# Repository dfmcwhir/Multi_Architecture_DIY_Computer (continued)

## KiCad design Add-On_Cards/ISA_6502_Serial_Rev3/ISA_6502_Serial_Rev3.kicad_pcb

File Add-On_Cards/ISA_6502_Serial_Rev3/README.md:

#<h2> ISA_6502_Serial_Rev3 </h2>
<p>This is a new card that is in the process of being tested with the ISA_6502_CPU Rev2 card. It hasn't been tested at all with the ISA_6502_CPU rev1 or other CPU cards yet. It has the same 6551 ACIA chip and MAX232 serial interface, but now a PS2 keyboard and mouse interface has been moved to this board. The keyboard and mouse interfaces to the bus using an ATMEGA328 microcontroller. The code for the ATMEGA238 is based on Grant Searle code here: http://searle.x10host.com/MonitorKeyboard/index.html. The ATMEGA also provides a TTL serial console interface that can be read from and written to. This is for providing a UI when you don't have a keyboard and display hooked up to the computer without having to dedicate the card's main serial interface to that.</p>

<h2>Resources</h2>
<table><thead><tr><th>Address</th><th>Function</th></tr></thead>
<tr><td>7F14</td><td>Serial Data Register</td></tr>
<tr><td>7F15</td><td>Serial Status Register</td></tr>
<tr><td>7F16</td><td>Serial Command Register</td></tr>
<tr><td>7F17</td><td>Serial Control Register</td></tr>
<tr><td>7F1E</td><td>Read=KB/mouse data, Write=serial console out/td></tr>
<tr><td>7F1F</td><td>Read=KB status, D7=KBavail,D6=DBusy</td></tr>
</table>

<p>The 6551 uses IRQ3. The keyboard/mouse uses IRQ5 or 6 (selectable by a jumper). Previously, when the kb and the display were on one card it used IRQ5, but jumper allows for more flexibility.</p>

<h2>Testing Status:</h2>
<p>The KB and mouse interface has been tested and seems to work with the FW uploaded. The ACIA Serial and console serial hasn't been tested yet. It hasn't been tested with any CPU cards other than the 6502_CPU Rev2 card. </p>

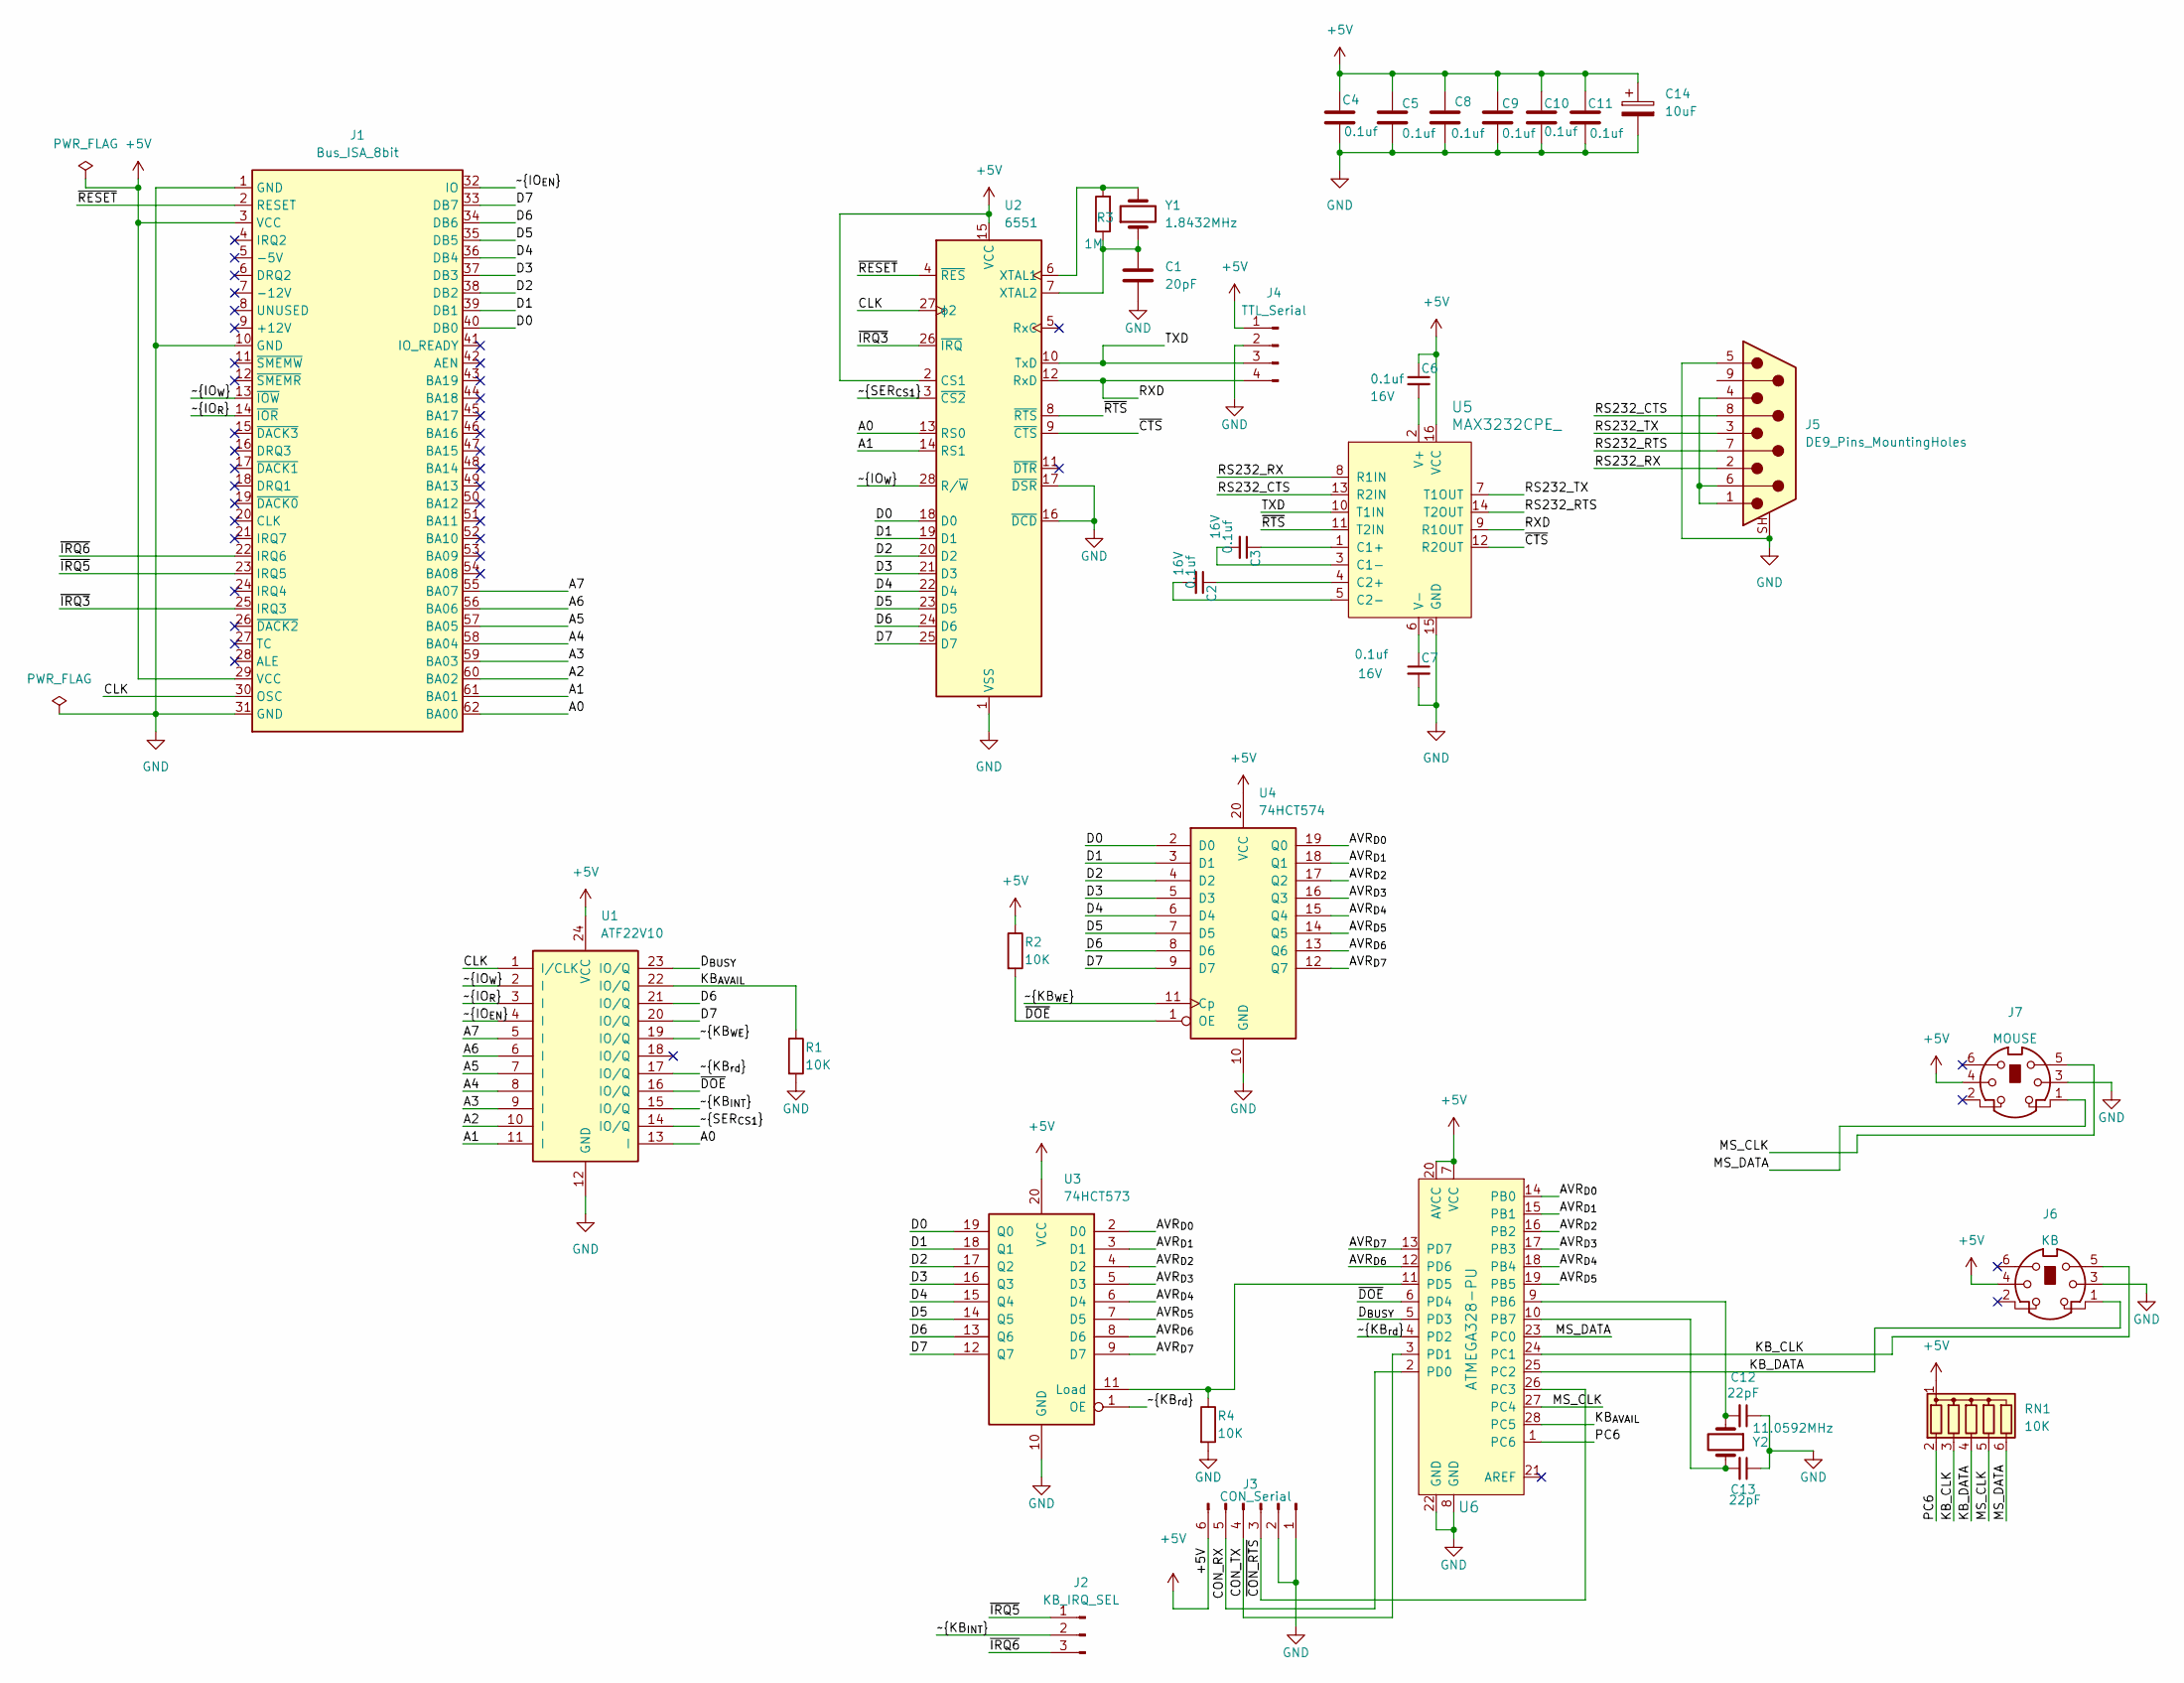
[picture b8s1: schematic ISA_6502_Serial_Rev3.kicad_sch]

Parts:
C1: 20pF; C_Disc_D4.7mm_W2.5mm_P5.00mm
C2, C3, C6, C7: 0.1uf; C_Disc_D4.7mm_W2.5mm_P5.00mm; Voltage 16V; Tolerance 100%
C4, C5, C8, C9, C10, C11: 0.1uf; C_Disc_D4.7mm_W2.5mm_P5.00mm
C12, C13: 22pF; C_Disc_D4.7mm_W2.5mm_P5.00mm; Voltage 50V; Tolerance 5%
C14: 10uF; CP_Radial_D5.0mm_P2.00mm
J1: Bus_ISA_8bit; BUS_8-bit_ISA_CARD
J2: KB_IRQ_SEL; PinHeader_1x03_P2.54mm_Vertical
J3: CON_Serial; PinHeader_1x06_P2.54mm_Vertical
J4: TTL_Serial; PinHeader_1x04_P2.54mm_Vertical
J5: DE9_Pins_MountingHoles; DSUB-9_Pins_Horizontal_P2.77x2.84mm_EdgePinOffset7.70mm_Hou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
J6: KB; Connector_Mini-DIN_Female_6Pin_2rows
J7: MOUSE; Connector_Mini-DIN_Female_6Pin_2rows
R1, R2, R4: 10K; R_Axial_DIN0207_L6.3mm_D2.5mm_P10.16mm_Horizontal
R3: 1M; R_Axial_DIN0207_L6.3mm_D2.5mm_P10.16mm_Horizontal
RN1: 10K; R_Array_SIP6
U1: ATF22V10; DIP-24_W7.62mm
U2: 6551; DIP-28_W15.24mm
U3: 74HCT573; DIP-20_W7.62mm
U4: 74HCT574; DIP-20_W7.62mm
U5: MAX3232CPE_; DIP-16_W7.62mm; MPN MAX3232CPE+; Digi-Key_PN MAX3232CPE+-ND
U6: ATMEGA328-PU; DIP-28_W7.62mm_Socket; MPN ATMEGA328-PU; Digi-Key_PN ATMEGA328-PU-ND
Y1: 1.8432MHz; Crystal_HC18-U_Vertical
Y2: 11.0592MHz; Crystal_HC18-U_Vertical

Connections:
+5V: C4.1, C5.1, C6.1, C8.1, C9.1, C10.1, C11.1, C14.1, J1.3 (VCC), J1.29 (VCC), J3.6, J4.1, J6.4, J7.4, R2.1, RN1.1 (common), U1.24 (VCC), U2.2 (CS1), U2.15 (VCC), U3.20 (VCC), U4.20 (VCC), U5.16 (VCC), U6.7 (VCC), U6.20 (AVCC)
/A0: J1.62 (BA00), U1.13 (I), U2.13 (RS0)
/A1: J1.61 (BA01), U1.11 (I), U2.14 (RS1)
/A2: J1.60 (BA02), U1.10 (I)
/A3: J1.59 (BA03), U1.9 (I)
/A4: J1.58 (BA04), U1.8 (I)
/A5: J1.57 (BA05), U1.7 (I)
/A6: J1.56 (BA06), U1.6 (I)
/A7: J1.55 (BA07), U1.5 (I)
/AVR_{D0}: U3.2 (D0), U4.19 (Q0), U6.14 (PB0)
/AVR_{D1}: U3.3 (D1), U4.18 (Q1), U6.15 (PB1)
/AVR_{D2}: U3.4 (D2), U4.17 (Q2), U6.16 (PB2)
/AVR_{D3}: U3.5 (D3), U4.16 (Q3), U6.17 (PB3)
/AVR_{D4}: U3.6 (D4), U4.15 (Q4), U6.18 (PB4)
/AVR_{D5}: U3.7 (D5), U4.14 (Q5), U6.19 (PB5)
/AVR_{D6}: U3.8 (D6), U4.13 (Q6), U6.12 (PD6)
/AVR_{D7}: U3.9 (D7), U4.12 (Q7), U6.13 (PD7)
/CLK: J1.30 (OSC), U1.1 (I/CLK), U2.27 (ϕ2)
/CON_RX: J3.5, U6.2 (PD0)
/CON_TX: J3.4, U6.3 (PD1)
/D0: J1.40 (DB0), U2.18 (D0), U3.19 (Q0), U4.2 (D0)
/D1: J1.39 (DB1), U2.19 (D1), U3.18 (Q1), U4.3 (D1)
/D2: J1.38 (DB2), U2.20 (D2), U3.17 (Q2), U4.4 (D2)
/D3: J1.37 (DB3), U2.21 (D3), U3.16 (Q3), U4.5 (D3)
/D4: J1.36 (DB4), U2.22 (D4), U3.15 (Q4), U4.6 (D4)
/D5: J1.35 (DB5), U2.23 (D5), U3.14 (Q5), U4.7 (D5)
/D6: J1.34 (DB6), U1.21 (IO/Q), U2.24 (D6), U3.13 (Q6), U4.8 (D6)
/D7: J1.33 (DB7), U1.20 (IO/Q), U2.25 (D7), U3.12 (Q7), U4.9 (D7)
/D_{BUSY}: U1.23 (IO/Q), U6.5 (PD3)
/KB_CLK: J6.5, RN1.3 (R2), U6.24 (PC1)
/KB_DATA: J6.1, RN1.4 (R3), U6.25 (PC2)
/KB_{AVAIL}: R1.1, U1.22 (IO/Q), U6.28 (PC5)
/MS_CLK: J7.5, RN1.5 (R4), U6.27 (PC4)
/MS_DATA: J7.1, RN1.6 (R5), U6.23 (PC0)
/PC6: RN1.2 (R1), U6.1 (PC6)
/RS232_CTS: J5.8, U5.13 (R2IN)
/RS232_RTS: J5.7, U5.14 (T2OUT)
/RS232_RX: J5.2, U5.8 (R1IN)
/RS232_TX: J5.3, U5.7 (T1OUT)
/RXD: J4.4, U2.12 (RxD), U5.9 (R1OUT)
/TXD: J4.3, U2.10 (TxD), U5.10 (T1IN)
/~CON_RTS: J3.3, U6.26 (PC3)
/~CTS: U2.9 (~CTS), U5.12 (R2OUT)
/~DOE: R2.2, U1.16 (IO/Q), U4.1 (OE), U6.6 (PD4)
/~IO_{EN}: J1.32 (IO), U1.4 (I)
/~IO_{R}: J1.14 (~IOR), U1.3 (I)
/~IO_{W}: J1.13 (~IOW), U1.2 (I), U2.28 (R/~W)
/~IRQ3: J1.25 (IRQ3), U2.26 (~IRQ)
/~IRQ5: J1.23 (IRQ5), J2.1
/~IRQ6: J1.22 (IRQ6), J2.3
/~KB_{INT}: J2.2, U1.15 (IO/Q)
/~KB_{WE}: U1.19 (IO/Q), U4.11 (Cp)
/~KB_{rd}: U1.17 (IO/Q), U3.1 (OE), U6.4 (PD2)
/~RESET: J1.2 (RESET), U2.4 (~RES)
/~RTS: U2.8 (~RTS), U5.11 (T2IN)
/~SER_{CS1}: U1.14 (IO/Q), U2.3 (~CS2)
GND: C1.2, C4.2, C5.2, C7.2, C8.2, C9.2, C10.2, C11.2, C12.1, C13.1, C14.2, J1.1 (GND), J1.10 (GND), J1.31 (GND), J3.1, J3.2, J4.2, J5.5, J5.SH (PAD), J6.3, J7.3, R1.2, R4.2, U1.12 (GND), U2.1 (VSS), U2.16 (~DCD), U2.17 (~DSR), U3.10 (GND), U4.10 (GND), U5.15 (GND), U6.8 (GND), U6.22 (GND)
unnamed: J5.1, J5.4, J5.6
unnamed: R3.2, U2.6 (XTAL1), Y1.2
unnamed: C1.1, R3.1, U2.7 (XTAL2), Y1.1
unnamed: R4.1, U3.11 (Load), U6.11 (PD5)
unnamed: C3.1, U5.1 (C1+)
unnamed: C3.2, U5.3 (C1-)
unnamed: C2.1, U5.4 (C2+)
unnamed: C2.2, U5.5 (C2-)
unnamed: C6.2, U5.2 (V+)
unnamed: C7.1, U5.6 (V-)
unnamed: C12.2, U6.9 (PB6), Y2.1
unnamed: C13.2, U6.10 (PB7), Y2.2

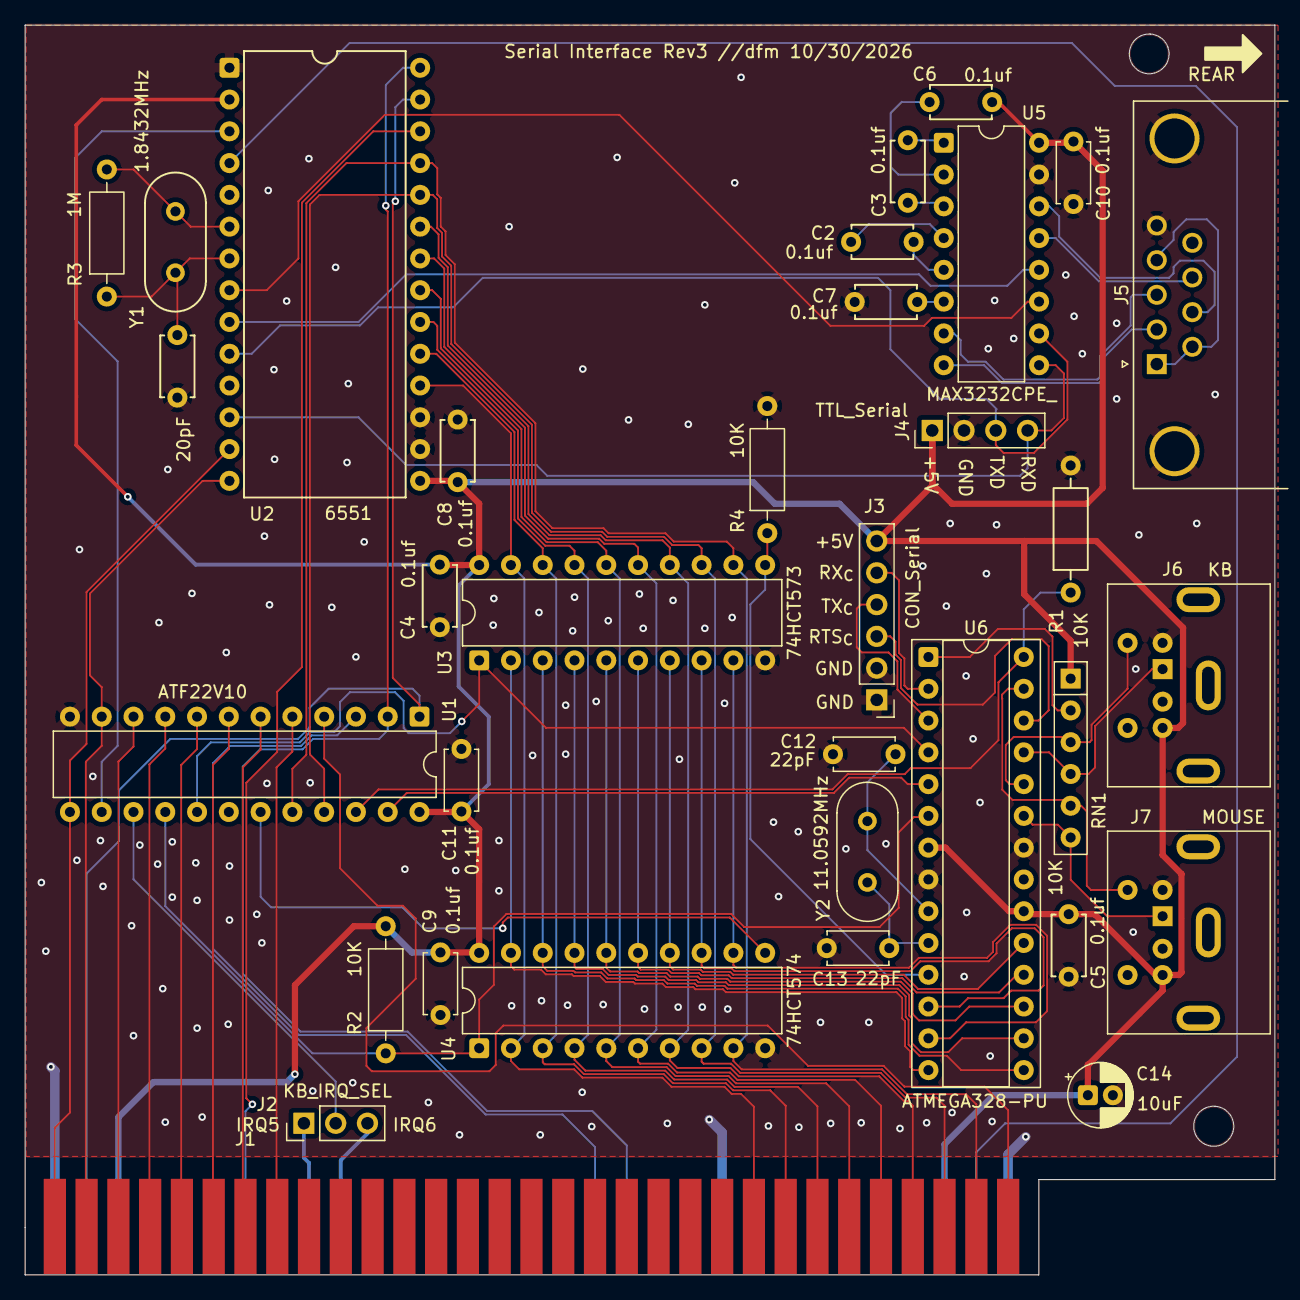
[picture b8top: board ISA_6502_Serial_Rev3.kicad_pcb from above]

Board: 2 copper layers, 99.9 x 99.9 mm, 34 parts (0 on the bottom side), 69 nets.

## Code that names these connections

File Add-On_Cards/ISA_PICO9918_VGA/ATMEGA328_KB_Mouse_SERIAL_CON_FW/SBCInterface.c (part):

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// The display output of the original (8-bit, 4-bit and TWI display links and
// the ANSI interpreter) has been removed - the PICO9918 is the display now.
//
// Version 2: adds a PS/2 mouse on PC4 (clock) and PC0 (data).
// Version 2.1: host -> device bytes (the mouse's reset and enable, the
//   keyboard's LED command) are clocked out on the falling edges, as the
//   PS/2 standard says; v2.0 was one clock edge off, so the mouse was never
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//
// ATmega328P pin use (DIP-28, 11.0592 MHz crystal)
// ------------------------------------------------
//   PB0-PB5  AVR bus D0-D5  (to '573 D inputs and '574 Q outputs)
//   PD6-PD7  AVR bus D6-D7
//   PB6-PB7  crystal
//   PC0      MOUSE DATA  (pull-up 4.7k-10k)   - was the optional /CTS input
//   PC1      KB clock    (pull-up)
//   PC2      KB data     (pull-up)
//   PC3      /RTS out
//   PC4      MOUSE CLOCK (pull-up 4.7k-10k)
//   PC5      KBAVAIL out -> GAL pin 14   (10k pull-down)
//   PC6      /RESET - keep it as reset (using it as I/O needs the RSTDISBL
//            fuse, which stops ISP programming)
//   PD0      RXD
//   PD1      TXD
//   PD2      INT0 <- /KBRD (GAL pin 17)  - byte acknowledge
//   PD3      <- DBUSY (GAL pin 22)       - 6502 has written a TX byte
//   PD4      /DOE  -> '574 /OE and GAL pin 23 (10k pull-up)
//   PD5      LE    -> '573 LE (10k pull-down)
//
// Handshakes
// ----------
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#include <stdint.h>

// ---------------------------------------------------------------- pins
#define KBAVAIL_BIT  PC5
#define RTS_BIT      PC3
#define KB_CLK_BIT   PC1
#define KB_DATA_BIT  PC2
#define MS_CLK_BIT   PC4
#define MS_DATA_BIT  PC0
#define DBUSY_BIT    PD3
#define DOE_BIT      PD4
#define LE_BIT       PD5

#define BUS_B_MASK   0x3F   // PB0-PB5 = D0-D5
#define BUS_D_MASK   0xC0   // PD6-PD7 = D6-D7

// ---------------------------------------------------------------- PS/2 devices
typedef struct
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		}
		else
		{
			d->writeActive = 0;                 // 11: the device's ack bit
			d->bitCount = 0;                    // (its rising edge is then
			d->shift = 0;                       //  ignored by the receiver)
		}
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	}
}

// Keyboard clock (PC1) and mouse clock (PC4) both raise PCINT1
ISR(PCINT1_vect)
{
	uint8_t pinc = PINC;
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	hostIn = hostOut = 0;
	txIn = txOut = 0;

	// AVR bus: inputs, no pull-ups (PB6/PB7 are the crystal)
	DDRB = 0x00;
	PORTB = 0x00;

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
	// Port D: /DOE high (set before enabling the output), LE low,
	// pull-up on the /KBRD input
	PORTD = (1 << DOE_BIT) | (1 << PD2);
	DDRD = (1 << PD1) | (1 << DOE_BIT) | (1 << LE_BIT);

	// Clear any DBUSY left set at power-up: hold /DOE low for a few clocks
	PORTD &= ~(1 << DOE_BIT);
	_delay_us(20);
	PORTD |= (1 << DOE_BIT);

	// PS/2 clocks: PC1 (keyboard) and PC4 (mouse) pin-change interrupts
	lastPinC = PINC;
	PCICR = 1 << PCIE1;
	PCMSK1 = (1 << PCINT9) | (1 << PCINT12);

	// INT0 (PD2, /KBRD) on rising edge = end of the 6502's read
	EICRA = (1 << ISC01) | (1 << ISC00);
	EIFR = 1 << INTF0;
	EIMSK = 1 << INT0;
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
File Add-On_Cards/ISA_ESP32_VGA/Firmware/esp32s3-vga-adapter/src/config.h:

// ESP32-S3 VGA / keyboard / mouse / sound adapter for a W65C02S computer.
// Pin map and build-time configuration.
//
// Board: ESP32-S3-DevKitC-1 (WROOM-1 N16R8 or N8R2 etc.). GPIO 33-37 are left
// free because octal-PSRAM modules use them. GPIO 19/20 are the native USB
// pins (USB host for keyboard/mouse). GPIO 43/44 stay as UART0 for upload and
// debug through the board's "UART" USB port.
#pragma once
#include <stdint.h>

// ---------------------------------------------------------------- 6502 bus
// All bus pins must be < 32 so one read of GPIO_IN_REG captures everything.
// D0..D7 must be consecutive GPIOs starting at PIN_D0.
#define PIN_D0        4     // D0..D7 = GPIO4..GPIO11 (via 74LVC8T245)
#define PIN_A0        12    // register select bit 0   (from GAL, open drain + 1k pull-up)
#define PIN_A1        13    // register select bit 1   (input)
#define PIN_RW        14    // R/W from CPU, 1 = read  (input)
#define PIN_NCS       15    // /CS for $7F18-$7F1B, decoded by the GAL, active low
#define PIN_PHI2      16    // PHI2 clock (input)
#define PIN_ACK       17    // to GAL ACK: 0 = hold RDY low while selected
#define PIN_IRQ       18    // to GAL IRQREQ: 1 = pull /IRQ low

// ---------------------------------------------------------------- VGA
// 2-bit-per-channel resistor DAC like FabGL (64 colours).
// Pixel byte format: 0b00RRGGBB.
#define PIN_VGA_B0    46
#define PIN_VGA_B1    45
#define PIN_VGA_G0    48
#define PIN_VGA_G1    47
#define PIN_VGA_R0    42
#define PIN_VGA_R1    41
#define PIN_VGA_HSYNC 39
#define PIN_VGA_VSYNC 40

// ---------------------------------------------------------------- PS/2
// Through a BSS138 4-channel bidirectional level shifter (5 V <-> 3.3 V).
#define PIN_KBD_CLK   1
#define PIN_KBD_DAT   2
#define PIN_MOUSE_CLK 21
#define PIN_MOUSE_DAT 3

// ---------------------------------------------------------------- Audio
// Sigma-delta output -> RC low-pass filter -> amplifier / line out.
#define PIN_AUDIO     38

// ---------------------------------------------------------------- Video timing
// 640x480 @ 60 Hz industry standard timing, negative sync polarity.
#define VGA_PCLK_HZ   25175000
#define VGA_H_RES     640
#define VGA_V_RES     480
#define VGA_HFP       16
#define VGA_HSYNC     96
#define VGA_HBP       48
#define VGA_VFP       10
#define VGA_VSYNC     2
#define VGA_VBP       33
#define VGA_BOUNCE_LINES 8      // lines per bounce buffer (480 must be a multiple)

// Text layer: 80x30 cells of 8x16 pixels.
#define TEXT_COLS     80
#define TEXT_ROWS     30

// Bitmap layer: 320x240, 1 byte per pixel, shown pixel-doubled.
#define GFX_W         320
#define GFX_H         240

#define NUM_SPRITES   16
#define NUM_PATTERNS  32
#define SPRITE_SIZE   16

// Any colour byte with bit 6 set is transparent (sprites, text background).
#define COLOR_TRANSPARENT 0x40

// Size of the 6502 -> video command FIFO (entries, power of two).
#define VIDEO_FIFO_SIZE 16384

// ---------------------------------------------------------------- Audio synth
#define AUDIO_SAMPLE_RATE 31250
#define AUDIO_VOICES      4

#define FW_VERSION_MAJOR 1
#define FW_VERSION_MINOR 0
